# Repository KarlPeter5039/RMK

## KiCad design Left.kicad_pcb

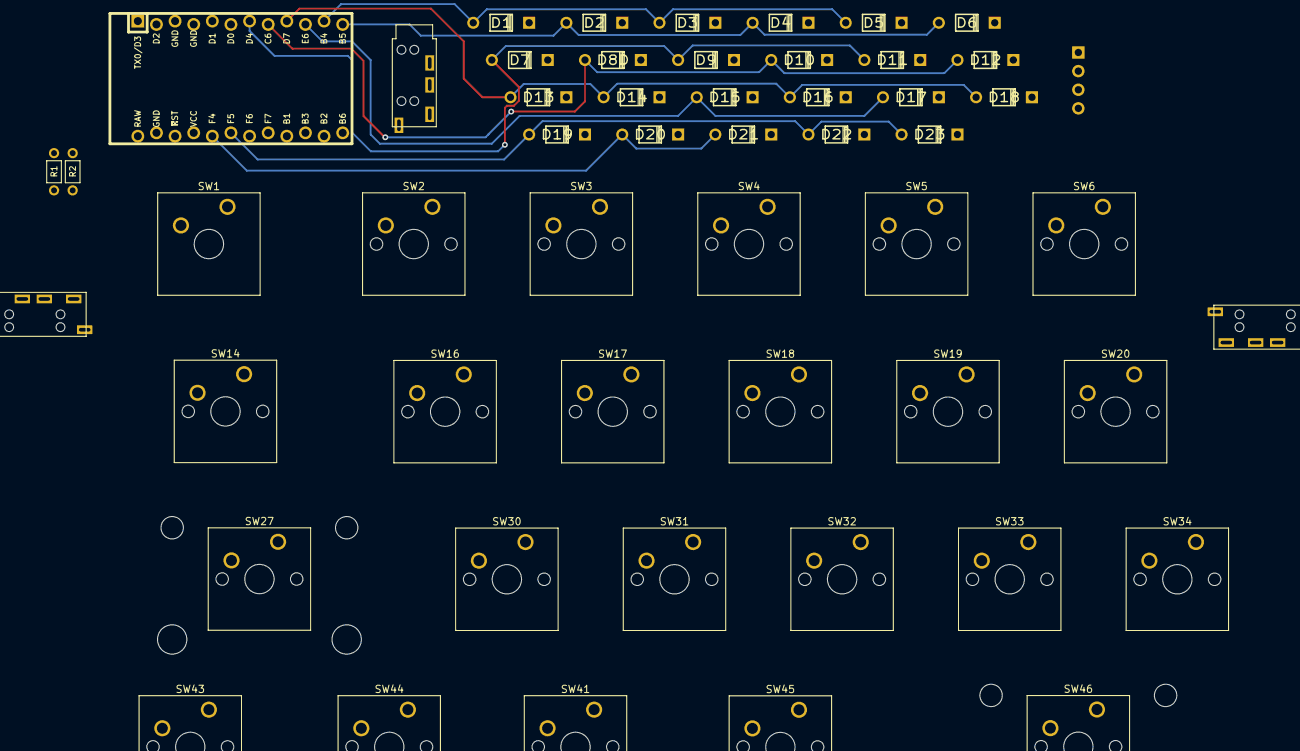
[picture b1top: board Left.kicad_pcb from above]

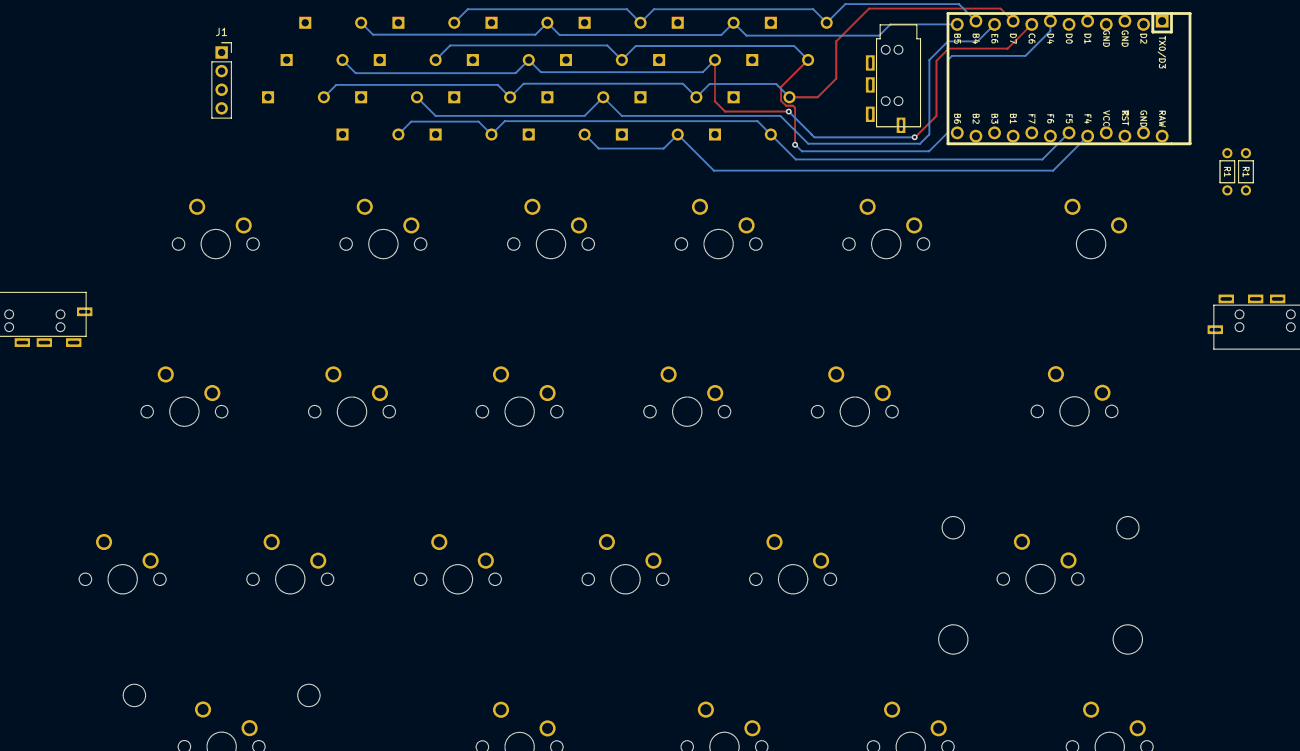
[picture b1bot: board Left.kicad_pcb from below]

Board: 2 copper layers, 53 parts (2 on the bottom side), 39 nets.

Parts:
D1, D2, D3, D4, D5, D6, D7, D8D, D9, D10, D11, D12, D13, D14, D15, D16, D17, D18, D19, D20, D21, D22, D23: VAL**; Diode
J1: Conn_01x04; PinSocket_1x04_P2.54mm_Vertical
J2, J2#2, J2#3: 4PIN; TRRS
R1, R2: R; RESISTOR
SW1: KEYSW; SW_Cherry_MX_1.50u_Plate
SW2, SW3, SW4, SW5, SW6, SW16, SW17, SW18, SW19, SW20, SW30, SW31, SW32, SW33, SW34, SW41, SW44: KEYSW; SW_Cherry_MX_1.00u_PCB
SW14: KEYSW; SW_Cherry_MX_1.75u_PCB
SW27, SW46: KEYSW; SW_Cherry_MX_2.25u_PCB
SW43, SW45: KEYSW; SW_Cherry_MX_1.25u_PCB
U1: ProMicro-18mil-offset; ArduinoProMicro-ZigZag

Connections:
GND: J1.1, J2.2, J2#2.2, J2#3.2, U1.3, U1.4, U1.23
unnamed: D1.2, SW1.2
unnamed: D2.2, SW2.2
unnamed: D3.2, SW3.2
unnamed: D4.2, SW4.2
unnamed: D5.2, SW5.2
unnamed: D6.2, SW6.2
unnamed: D7.2, SW14.2
unnamed: D8D.2, SW16.2
unnamed: D9.2, SW17.2
unnamed: D10.2, SW18.2
unnamed: D11.2, SW19.2
unnamed: D12.2, SW20.2
unnamed: D13.2, SW27.2
unnamed: D14.2, SW30.2
unnamed: D15.2, SW31.2
unnamed: D16.2, SW32.2
unnamed: D17.2, SW33.2
unnamed: D18.2, SW34.2
unnamed: D19.2, SW43.2
unnamed: D20.2, SW44.2
unnamed: D22.2, SW45.2
unnamed: D23.2, SW46.2
unnamed: D21.2, SW41.2
SCL: J1.3, J2.4, J2#2.4, J2#3.4, R2.2, U1.6
SDA: J1.4, J2.3, J2#2.3, J2#3.3, R1.2, U1.5
VCC: J1.2, J2.1, J2#2.1, J2#3.1, R1.1, R2.1, U1.21
col0: SW1.1, SW2.1, SW14.1, SW16.1, SW27.1, SW43.1, SW44.1, U1.18
col1: SW3.1, SW4.1, SW17.1, SW18.1, SW30.1, SW31.1, SW45.1, U1.17
col2: SW5.1, SW6.1, SW19.1, SW20.1, SW32.1, SW33.1, SW41.1, SW46.1, U1.16
col3: SW34.1, U1.15
rowA: D1.1, D3.1, D5.1, U1.11
rowB: D2.1, D4.1, D6.1, U1.12
rowC: D7.1, D9.1, D11.1, U1.7
rowD: D8D.1, D10.1, D12.1, U1.8
rowE: D13.1, D14.1, D16.1, D18.1, U1.9
rowF: D15.1, D17.1, U1.10
rowG: D19.1, D22.1, D23.1, U1.19
rowH: D20.1, D21.1, U1.20

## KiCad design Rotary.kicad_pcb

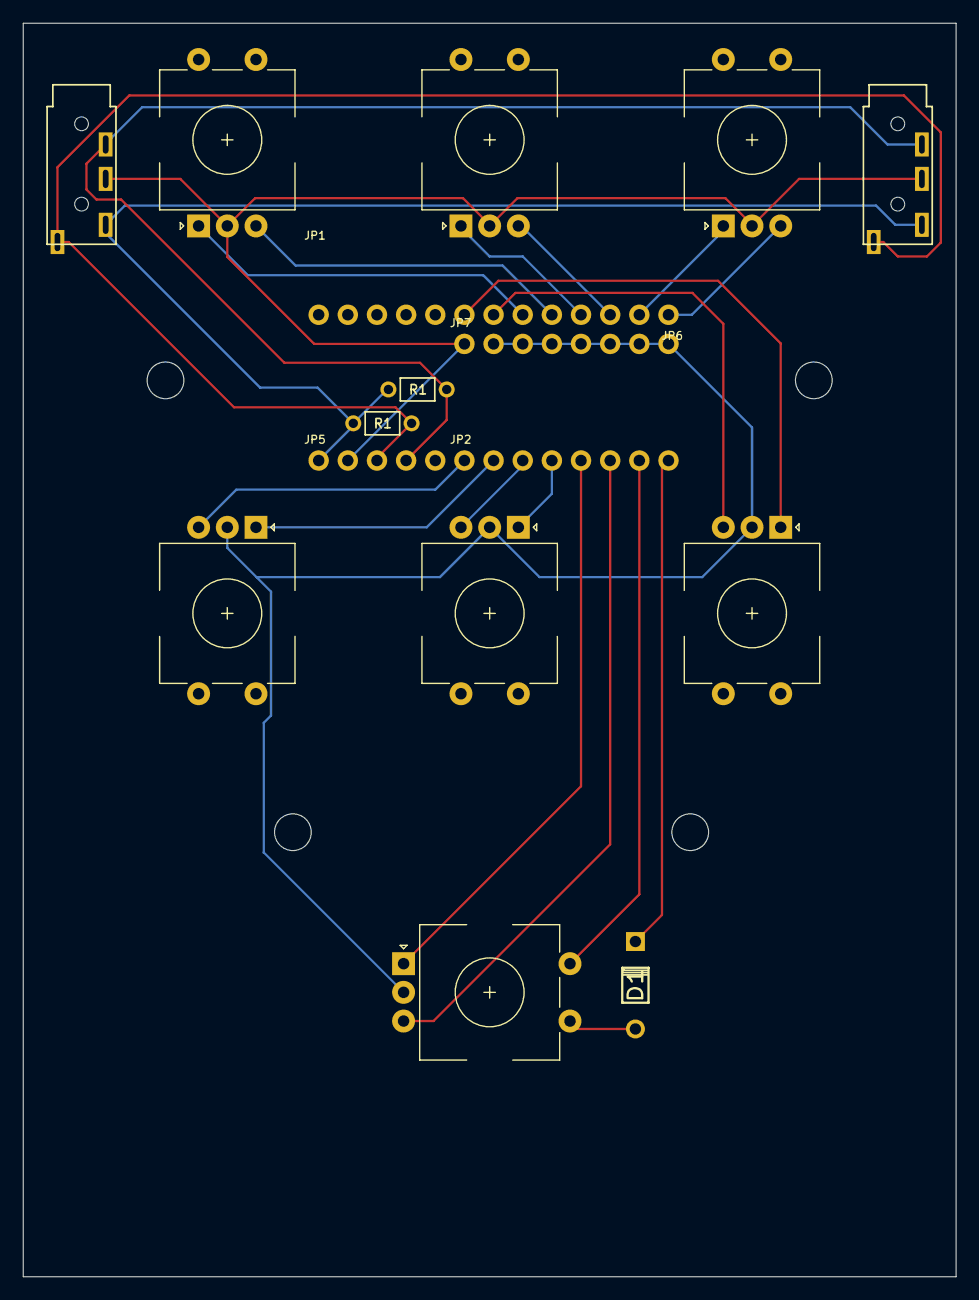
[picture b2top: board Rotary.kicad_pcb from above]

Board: 2 copper layers, 81.3 x 109.2 mm, 10 parts (0 on the bottom side), 5 nets.

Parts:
D1: VAL**; Diode
J2, J2#2: 4PIN; TRRS
JP1, JP5: 1X05_ROUND_70
JP2, JP6, JP7: 1X08_ROUND_70
R1, R1#2: R; RESISTOR

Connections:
GND: J2.2, J2#2.2, JP5.2, JP7.1, JP7.2, JP7.3, JP7.4, JP7.5, JP7.6, JP7.7, JP7.8
SCL: J2.4, J2#2.4, JP5.3, R1.1
SDA: J2.3, J2#2.3, JP5.4, R1#2.1
VCC: J2.1, J2#2.1, JP5.1, R1.2, R1#2.2
row0: D1.2, JP2.8

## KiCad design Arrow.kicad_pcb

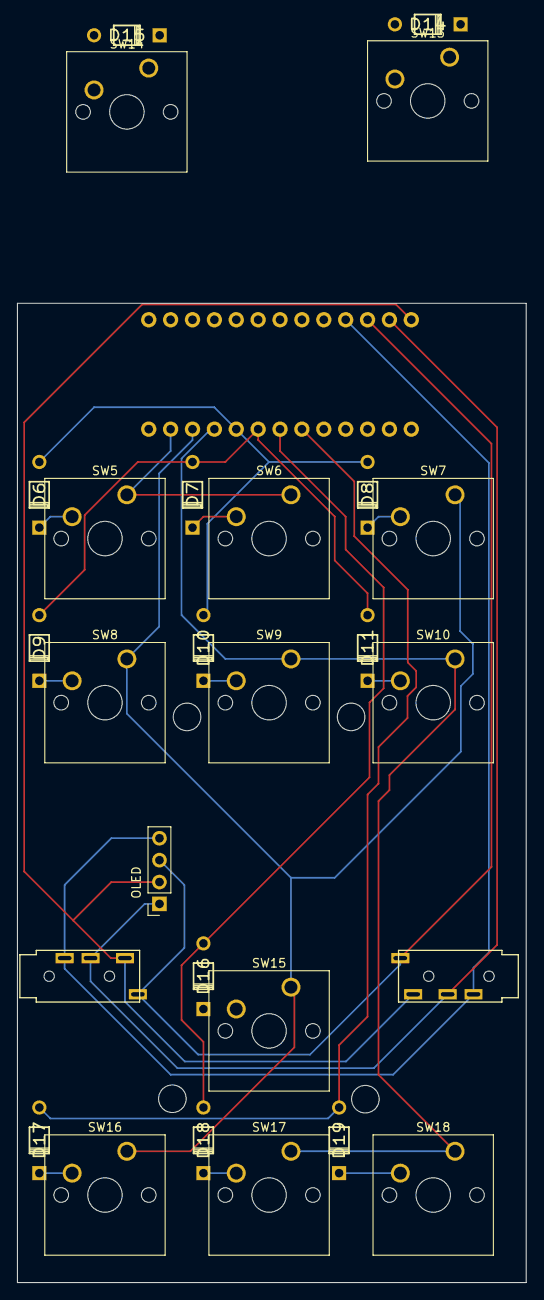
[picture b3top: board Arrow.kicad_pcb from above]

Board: 2 copper layers, 59.1 x 113.7 mm, 31 parts (0 on the bottom side), 23 nets.

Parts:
D6, D7, D8, D9, D10, D11, D14, D15, D16, D17, D18, D19: D_Small; Diode
J1: Conn_01x04; PinSocket_1x04_P2.54mm_Vertical
J2, J2#2: 4PIN; TRRS
JP1, JP5: 1X05_ROUND_70
JP2, JP6: 1X08_ROUND_70
SW5, SW6, SW7, SW8, SW9, SW10, SW13, SW14, SW15, SW16, SW17, SW18: KEYSW; SW_Cherry_MX_1.00u_PCB

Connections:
GND: J1.1, J2.2, J2#2.2, JP5.2
unnamed: D6.2 (A), SW5.2
unnamed: D7.2 (A), SW6.2
unnamed: D8.2 (A), SW7.2
unnamed: D9.2 (A), SW8.2
unnamed: D10.2 (A), SW9.2
unnamed: D11.2 (A), SW10.2
unnamed: D14.2 (A), SW13.2
unnamed: D15.2 (A), SW14.2
unnamed: D16.2 (A), SW15.2
unnamed: D17.2 (A), SW16.2
unnamed: D18.2 (A), SW17.2
unnamed: D19.2 (A), SW18.2
SCL: J1.3, J2.4, J2#2.4, JP5.3
SDA: J1.4, J2.3, J2#2.3, JP5.4
VCC: J1.2, J2.1, J2#2.1, JP5.1
c1: JP6.2, SW5.1, SW6.1, SW13.1, SW14.1
c2: JP6.3, SW7.1, SW8.1, SW15.1, SW16.1
c3: JP6.4, SW9.1, SW10.1, SW17.1, SW18.1
r0: D6.1 (K), D8.1 (K), D10.1 (K), JP6.5
r1: D7.1 (K), D9.1 (K), D11.1 (K), JP6.6
r2: D14.1 (K), D16.1 (K), D18.1 (K), JP6.7
r3: D15.1 (K), D17.1 (K), D19.1 (K), JP6.8

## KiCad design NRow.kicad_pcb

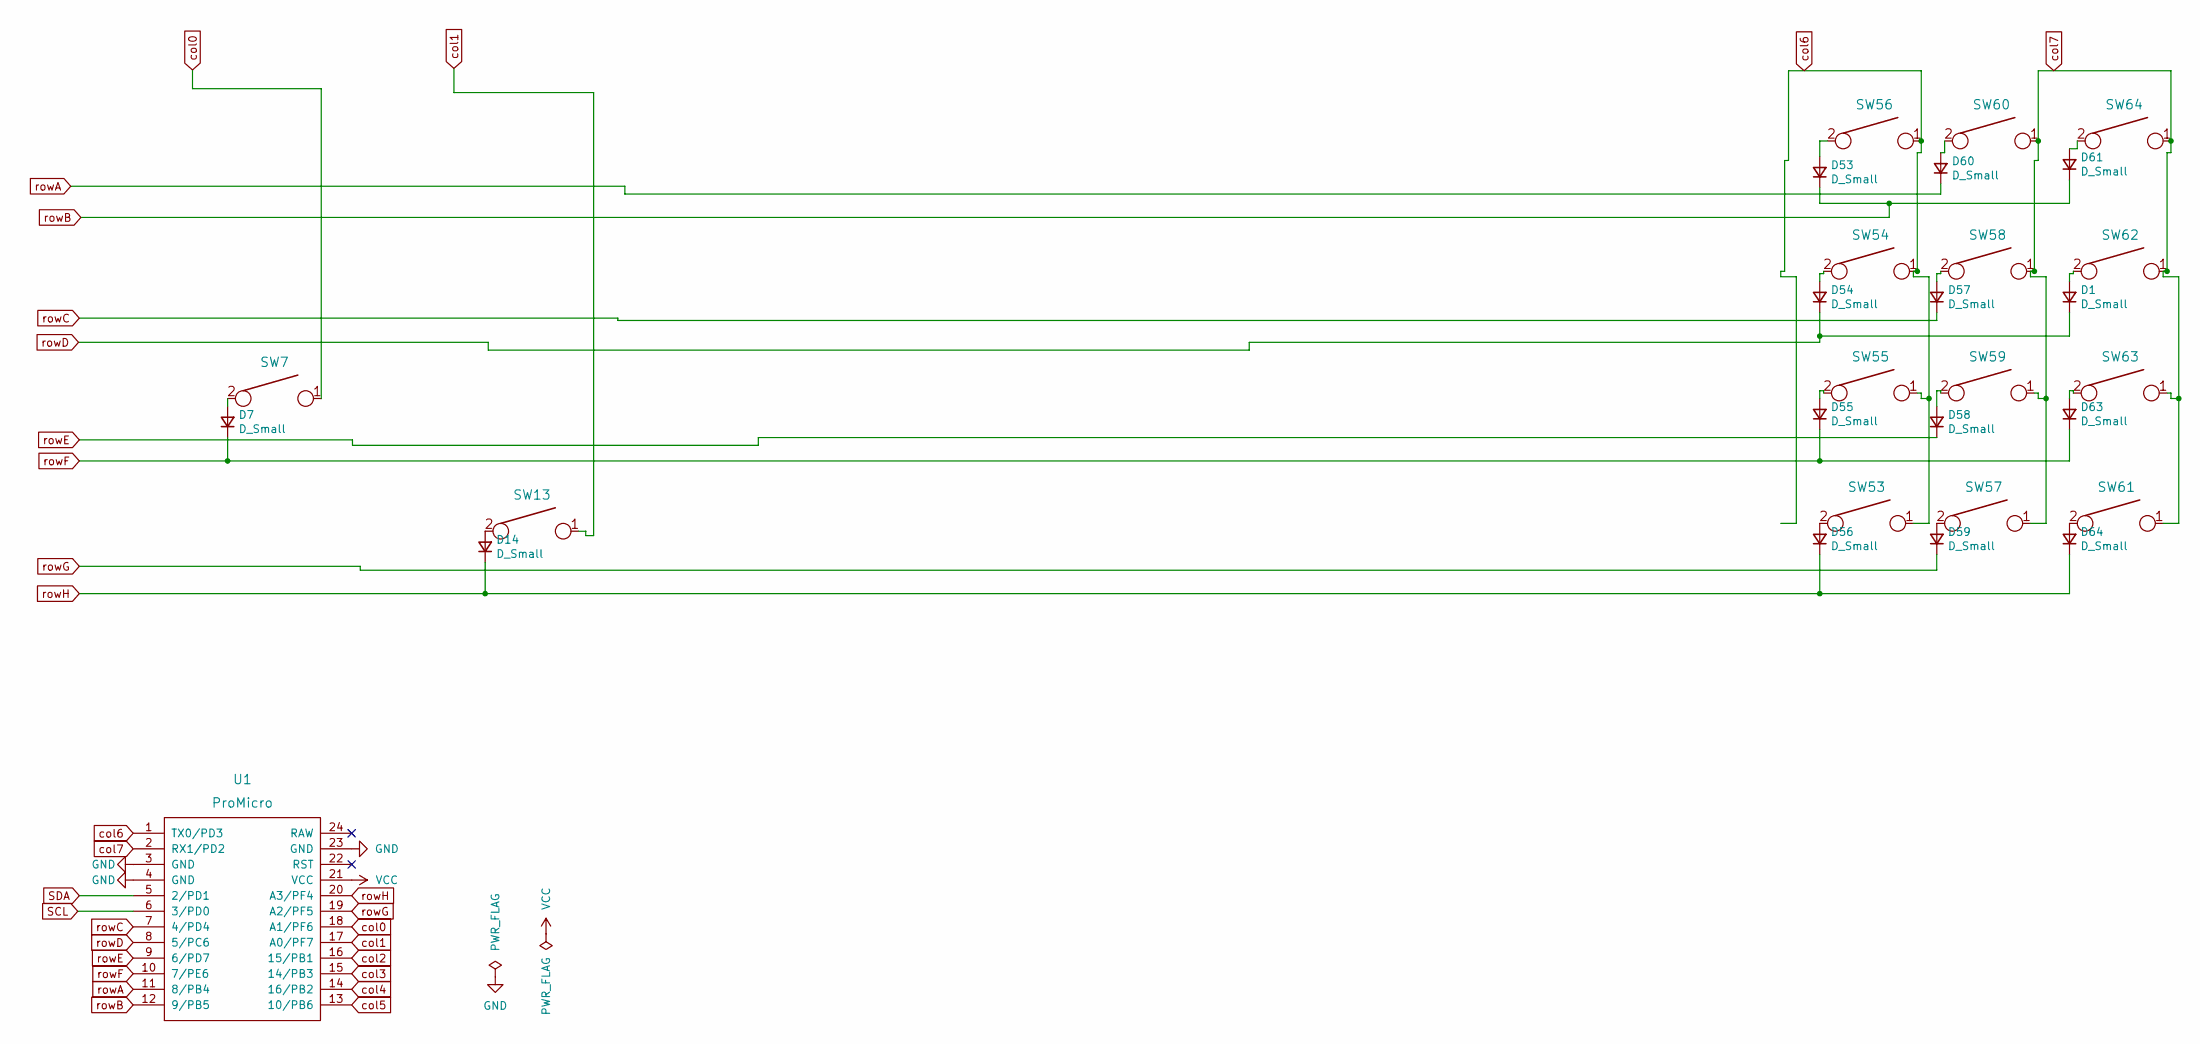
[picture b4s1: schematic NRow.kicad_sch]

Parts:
D1, D7, D14, D53, D54, D55, D56, D57, D58, D59, D60, D61, D63, D64: D_Small; Diode
SW7: KEYSW; SW_Cherry_MX_2.25u_PCB
SW13, SW53, SW54, SW55, SW56, SW57, SW58, SW59, SW60, SW61, SW62, SW63, SW64: KEYSW; SW_Cherry_MX_1.00u_PCB
U1: ProMicro; ArduinoProMicro-ZigZag

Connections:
GND: U1.3 (GND), U1.4 (GND), U1.23 (GND)
unnamed: D1.2 (A), SW62.2
unnamed: D7.2 (A), SW7.2
unnamed: D14.2 (A), SW13.2
unnamed: D53.2 (A), SW56.2
unnamed: D54.2 (A), SW54.2
unnamed: D55.2 (A), SW55.2
unnamed: D56.2 (A), SW53.2
unnamed: D57.2 (A), SW58.2
unnamed: D58.2 (A), SW59.2
unnamed: D59.2 (A), SW57.2
unnamed: D60.2 (A), SW60.2
unnamed: D61.2 (A), SW64.2
unnamed: D63.2 (A), SW63.2
unnamed: D64.2 (A), SW61.2
SCL: U1.6 (3/PD0)
SDA: U1.5 (2/PD1)
VCC: U1.21 (VCC)
col0: SW7.1, U1.18 (A1/PF6)
col1: SW13.1, U1.17 (A0/PF7)
col2: U1.16 (15/PB1)
col3: U1.15 (14/PB3)
col4: U1.14 (16/PB2)
col5: U1.13 (10/PB6)
col6: SW53.1, SW54.1, SW55.1, SW56.1, U1.1 (TX0/PD3)
col7: SW57.1, SW58.1, SW59.1, SW60.1, SW61.1, SW62.1, SW63.1, SW64.1, U1.2 (RX1/PD2)
rowA: D60.1 (K), U1.11 (8/PB4)
rowB: D53.1 (K), D61.1 (K), U1.12 (9/PB5)
rowC: D57.1 (K), U1.7 (4/PD4)
rowD: D1.1 (K), D54.1 (K), U1.8 (5/PC6)
rowE: D58.1 (K), U1.9 (6/PD7)
rowF: D7.1 (K), D55.1 (K), D63.1 (K), U1.10 (7/PE6)
rowG: D59.1 (K), U1.19 (A2/PF5)
rowH: D14.1 (K), D56.1 (K), D64.1 (K), U1.20 (A3/PF4)

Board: 2 copper layers, 31 parts (0 on the bottom side), 27 nets, no tracks yet.

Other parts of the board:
J2, J2#2: 4PIN; TRRS

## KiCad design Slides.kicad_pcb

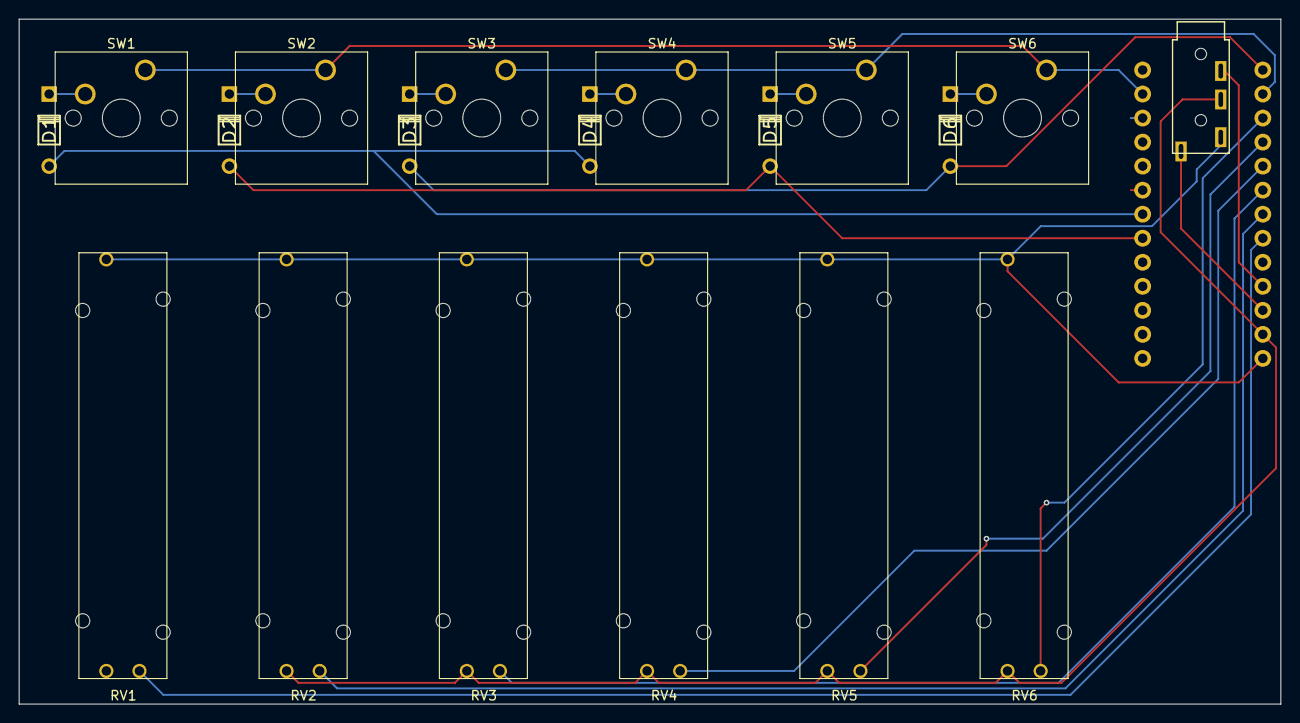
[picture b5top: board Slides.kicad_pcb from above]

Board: 2 copper layers, 133.3 x 72.4 mm, 23 parts (0 on the bottom side), 21 nets.

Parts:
D1, D2, D3, D4, D5, D6: D_Small; Diode
J2: 4PIN; TRRS
JP1, JP5: 1X05_ROUND_70
JP2, JP6: 1X08_ROUND_70
RV1, RV2, RV3, RV4, RV5, RV6: R_POT; potentiometer_slider_45mm
SW1, SW2, SW3, SW4, SW5, SW6: KEYSW; SW_Cherry_MX_1.00u_PCB

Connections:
GND: J2.2, JP5.2, RV1.1, RV2.1, RV3.1, RV4.1, RV5.1, RV6.1
unnamed: D1.2 (A), SW1.2
unnamed: D2.2 (A), SW2.2
unnamed: D3.2 (A), SW3.2
unnamed: D4.2 (A), SW4.2
unnamed: D5.2 (A), SW5.2
unnamed: D6.2 (A), SW6.2
SCL: J2.4, JP5.3
SDA: J2.3, JP5.4
VCC: J2.1, JP5.1, RV1.3, RV2.3, RV3.3, RV4.3, RV5.3, RV6.3
c1: JP6.2, SW1.1, SW2.1, SW6.1
c4: JP2.7, SW3.1, SW4.1, SW5.1
potA: JP2.1, RV1.2
potB: JP2.2, RV2.2
potC: JP2.3, RV3.2
potD: JP2.4, RV4.2
potE: JP2.5, RV5.2
potF: JP2.6, RV6.2
r2: D1.1 (K), D4.1 (K), JP6.7
r3: D2.1 (K), D5.1 (K), JP6.8
r4: D3.1 (K), D6.1 (K), JP2.8

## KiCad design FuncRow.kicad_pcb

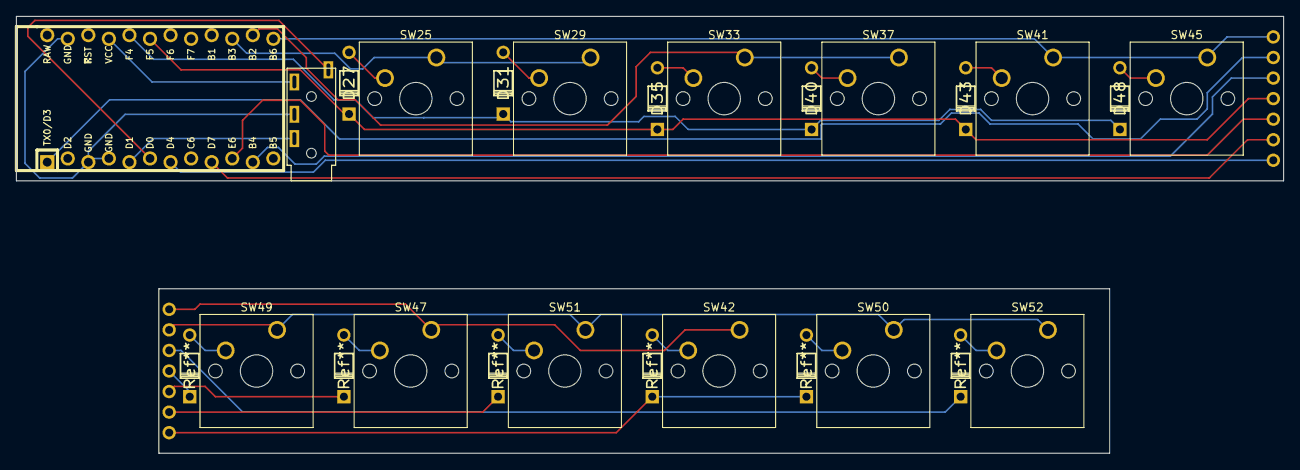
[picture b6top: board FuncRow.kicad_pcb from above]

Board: 2 copper layers, 156.6 x 54.0 mm, 26 parts (0 on the bottom side), 26 nets.

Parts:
D27, D31, D35, D40, D43, D48: VAL**; Diode
J2: 4PIN; TRRS
Ref**: VAL**; Diode
Ref**#2, Ref**#3, Ref**#4, Ref**#5, Ref**#6: VAL**; Diode
SW25, SW29, SW33, SW37, SW41, SW42, SW45, SW47, SW49, SW50, SW51, SW52: KEYSW; SW_Cherry_MX_1.00u_PCB
U1: ProMicro-18mil-offset; ArduinoProMicro-ZigZag

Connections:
GND: J2.2, U1.3, U1.4, U1.23
unnamed: D27.1, SW25.2
unnamed: D31.1, SW29.2
unnamed: D35.1, SW33.2
unnamed: D40.1, SW37.2
unnamed: Ref**#5.1, SW42.2
unnamed: D43.1, SW41.2
unnamed: Ref**#6.1, SW47.2
unnamed: D48.1, SW45.2
unnamed: Ref**#4.1, SW50.2
unnamed: Ref**#3.1, SW51.2
unnamed: Ref**#2.1, SW49.2
unnamed: Ref**.1, SW52.2
SCL: J2.4, U1.6
SDA: J2.3, U1.5
VCC: J2.1, U1.21
col3: SW25.1, SW29.1, U1.15
col4: SW33.1, SW37.1, U1.14
col5: SW41.1, SW42.1, SW45.1, SW47.1, U1.13
col6: SW49.1, SW50.1, SW51.1, SW52.1, U1.1
rowA: Ref**.2, U1.11
rowC: Ref**#4.2, Ref**#5.2, U1.7
rowE: Ref**#3.2, U1.9
rowF: Ref**#6.2, U1.10
rowG: D27.2, D35.2, D43.2, Ref**#2.2, U1.19
rowH: D31.2, D40.2, D48.2, U1.20
